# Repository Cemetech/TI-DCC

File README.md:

# TI-DCC
Is a z80 ASM NMRA-DCC throttle implementation for the TI-84 Plus C Silver Edition.

## Features
* Custom DCC throttle interface.  
* FL-F26 Function support with momentary/locking functions  
* 14/28/128 step speed modes  
* 2 Digit and 4 Digit addressing
 
## ToDo
* Analog/DC throttle mode - To be implmented.
* Verify 14/128 step speed modes
* Verify Long addresses work
* Finish Reccomended schematic

## Requirements
### Building
* Python 2.* and the python launcher. (comes with py3...)
* Pillow
### Use
* Motor driver - A motor driver/H-bridge and circuit used to generate the on rail signals for the train.
* Power supply for the motor driver. Voltage is based off of the scale train you plan on controlling. See the NMRA Standards linked at the bottom of this readme

## Known good motor drivers
* LMD18200 using this circuit [MiniDCC](http://www.minidcc.com/minibooster.gif)

## Installation 
1) run _buildclean.bat
2) Transfer application to calculator using TI-Connect or TILP

## Controls
### Configuration View
* NumberPad: Set Addresss
* F1-F3: set Speed steps mode
* F4: Set DC Controll mode
* F5: Save Changes
### Controller View
* Left/Right: Set Forward or Reverse movement
* Up/Down: Adjust throttle
* Number Pad: Control functions
* F1-F3: Switch between function banks
* CFG: Open configuration view
* Lock: Allows changing of function type
* Math: Quit
* Enter: E-Stop
* SIN: Change read out colors

## References
* Forum Topic: http://cemete.ch/p261712
* NMRA Documentation: https://www.nmra.org/index-nmra-standards-and-recommended-practices

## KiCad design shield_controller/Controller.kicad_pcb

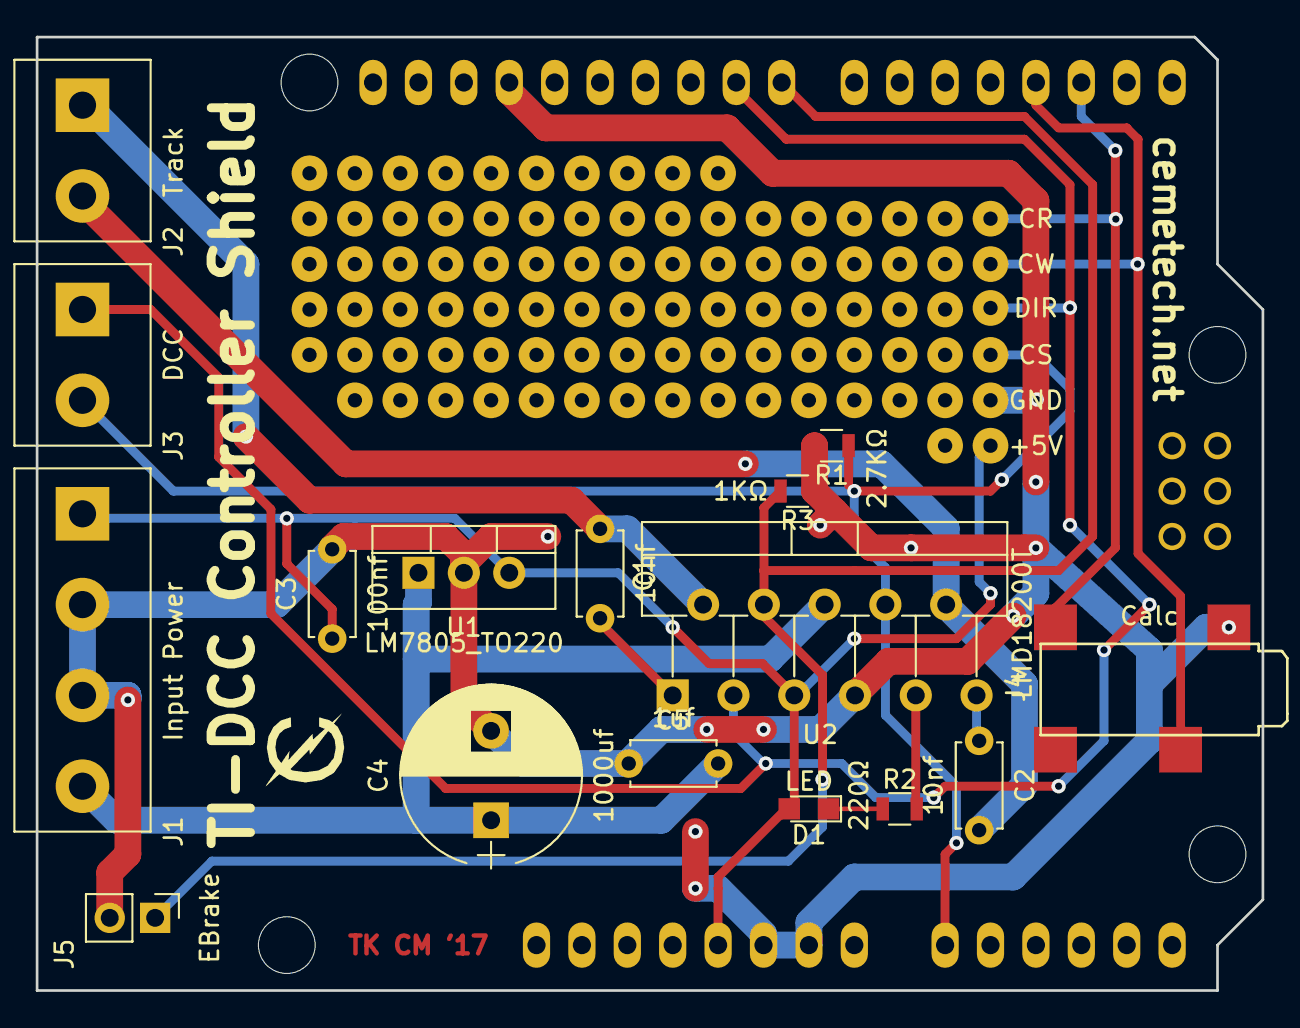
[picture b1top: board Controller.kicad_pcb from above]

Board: 2 copper layers, 68.6 x 53.3 mm, 17 parts (0 on the bottom side), 14 nets.

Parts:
C1, C2: 10nf; C_Disc_D4.7mm_W2.5mm_P5.00mm
C3: 100nf; C_Disc_D4.7mm_W2.5mm_P5.00mm
C4: 1000uf; CP_Radial_D10.0mm_P5.00mm
C5: 1uf; C_Disc_D4.7mm_W2.5mm_P5.00mm
D1: LED; LED_0805
J1: Input Power; TerminalBlock_bornier-4_P5.08mm
J2: Track; TerminalBlock_bornier-2_P5.08mm
J3: DCC; TerminalBlock_bornier-2_P5.08mm
J4: Calc; SJ-2523-SMT-TR
J5: EBrake; Pin_Header_Straight_1x02_Pitch2.54mm
R1: 2.7KΩ; R_0805
R2: 220Ω; R_0805
R3: 1KΩ; R_0805
SHIELD1: ARDUINO_SHIELD
U1: LM7805_TO220; TO-220-3_Vertical
U2: LMD18200T; TO-220-11_Vertical_StaggeredType1

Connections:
+5V: C3.1, D1.2, J1.1, SHIELD1.5V, U1.3, U2.5
+12V: C4.1, C5.1, J1.4, U1.1, U2.6
/Brake: J5.1, R3.2, SHIELD1.8, U2.4
/CalcRed: J4.2, SHIELD1.2
/CalcWhite: J4.3, SHIELD1.3
/Current_Sense: J3.2, R1.1, SHIELD1.AD0, U2.8
/Direction: J3.1, SHIELD1.9, U2.3
/Track1: C1.2, J2.1, U2.2
/Track2: C2.2, J2.2, U2.10
GND: C3.2, C4.2, C5.2, J1.2, J1.3, J4.1, J5.2, R1.2, R3.1, SHIELD1.GND1, SHIELD1.GND2, SHIELD1.GND3, U1.2, U2.7
unnamed: C1.1, U2.1
unnamed: C2.1, U2.11
unnamed: D1.1, R2.1
unnamed: R2.2, U2.9

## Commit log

2017-07-30 Added test for testing signal generation timing interrupts.
2017-07-30 Corrected N++ tab/spacing
2017-07-30 Pedantic capitalization
2017-07-30 Various tidying, mostly comments and random numbers
2017-07-30 Discussion notes on interrupt structure
2017-08-09 Add start of structure/include file Add flow chart Format/cleanup code again
2017-08-10 Added bit level interrupt code Updated structs with relavant code.
2017-08-12 Lots of changes. See file comments. Not working
2017-08-12 Removed include.inc due to brass issues Fixed bit ordering on idle packet Updated Flow Chart
2017-08-19 Interface display can now refresh based on internal state
2017-08-19 Undid bank limiter and added graphic assets to render it
2017-08-20 Event loop added with F1-F3 F5 keys, numpad for lock only
2017-08-20 Fixed hardware gfx issue, partial numpad support (lock only)
2017-08-20 Forgot to push kbd.z80
2017-08-20 Fixed Momentary keys. GetCSC enabled interrupts. Added get CSC clone from Wikiti
2017-08-20 key debouncing works, full function support
2017-08-20 Internal documentation update
2017-08-20 fwd/rev w/ events added. accel/decel w/ events added
2017-08-20 Added start of controller schematic. Added packet generation code
2017-08-20 Added documentation and example code for event subscriptions
2017-08-21 Re-arrange files
2017-08-21 Partial implement for config screen
2017-08-21 Added Reverser Handler Added 14 and 28 Speed step handlers Move some code around for clarity Remove Extra LUT generator
2017-08-21 Added config screen, cleaned code up, made vars global, added estop, updated docs
2017-08-22 Address input added, long/short address supported
2017-08-22 Moved _mockup1.png, changed exitApp to Math key. Optimized images for size
2017-08-22 Exiting config now clears all function states
2017-08-22 Added e_estop event example in main.z80
2017-08-22 Added attributions, 7-seg color toggle, optimized routine size
2017-08-22 Fixed address bounds check to disallow 16384-16389
2017-08-22 Changed tabs in controller to match instructions
2017-08-22 Fixed sprite routine, optimized ctrl, tweaked image assets
2017-08-22 Nudged keypad right by one pixel
2017-08-22 Condensed graphics assets by one page
2017-08-23 Added packetPrepare function fixed send3bytepacket function adjusted insertbit for actual inputs
2017-08-23 Optimization to dccSendShort3byte
2017-09-14 Added partial support for numpad handler (fn grp 1,2)
2017-09-15 Added F13-F20,F21-F28 support, partial refactor
2017-09-15 Implemented 128sp, added interrupt cleanup, limit 126 speed
2017-09-15 resolved variable conflict
2017-09-15 fixed bad event call, display on E_STOP
2017-09-16 add CFG screen handler Fix _28speed to correctly generate packets Add testpacket
2017-09-16 Fixed speed limits
2017-09-17 Fix destruction of dccState.flags Add eStop
2017-09-18 Added better key debouncing, extended e_updown event
2017-09-18 Further extended e_updown to provide throttle mode
2017-09-18 bugfixes in numpad event
2017-09-19 Clean up packet sending. Add config for alloweing a +DCV on the rails
2017-09-19 Simplified PreparePacket for possible bug fix
2017-09-19 Set function state to default lock
2017-09-19 Tentative long address support added
2017-09-19 Long address bugfix
2017-09-19 Tweaked controller graphics/controls , reset address on config entry
2017-09-20 Updated ReadMe Updated on calculator readme
2017-09-20 Added low battery protection (quick exit)
2017-09-20 Tweaked 7-seg colors
2017-09-22 Added low memory guard
2017-09-22 Special version for Maker Faire. Changelog in MAKER_FAIRE_CHANGES.txt
2017-09-22 Removed backup file
2017-09-22 Added more restrictions.
2017-09-22 Added rounded segments for 7 seg display
2017-09-22 Removed backup, added rounded segments for 7seg display
2017-09-22 Re-locked exit, added default configuration spec
2017-12-12 Finished schematic. Designed board.
2017-12-12 Fixed wrong foot print selection for large filter capacitor Adjusted silkscreen mask
2017-12-21 Versioning Christopher's Arduino shield controller board
2018-01-25 Fixed shortcomings of MINIDCC booster board.
2018-01-25 Added silk screen text. Fixed fubars from last commit.
2018-01-30 DC mode interface lockout, dcmode change event added
2018-01-31 Set const speed step limit for DC mode
2018-02-08 Adjusted LED colors
2018-02-17 Updating Christopher's shield controller to current fabbed version
2018-02-17 Added initial code for DC mode
2018-09-23 Fixed duty cycle
